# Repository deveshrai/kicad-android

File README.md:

<div align="center">

# KiCad Android

**The real KiCad 10.99 EDA suite for Android and Googlebook OS, running natively on tablets,
foldables and laptops.**

Schematics, PCB layout with the interactive router, 3D viewer and Gerber output, built from
upstream KiCad sources.

-314CB0)

<sub>An ESP32-S3 board in Arduino Uno format, designed on a Galaxy Tab S12+ from an empty schematic to Gerbers, every step driven by Claude Code through KiCad's built-in MCP server.  The screens are real screenshots, from the Android emulator in a laptop-shaped window and from the tablet, shown in drawn device frames.</sub>

</div>

> **Not an official KiCad release.**  This project is not affiliated with or endorsed by the KiCad
> project.  "KiCad" is a trademark of the KiCad project and is used here only to say what this
> software is built from.  Please report problems here, not on KiCad's issue tracker.

## Highlights

- **Full desktop KiCad, not a viewer.**  It includes the project manager, schematic editor, PCB
  editor and push-and-shove router, footprint and symbol editors, Gerber viewer, calculator and
  `kicad-cli`.
- **GPU canvas.**  It runs on KiCad's Vulkan backend, with pointer motion coalesced so the
  interactive router keeps up.
- **Two built-in autorouters.**  **Route > Autoroute** runs
  [KiCadRoutingTools](https://github.com/drandyhaas/KiCadRoutingTools) (Andy Haas's router, with
  its own Python, numpy and scipy) or [Freerouting](https://github.com/freerouting/freerouting) on
  the device.  [More below](#autoroute).
- **Built-in MCP server.**  Turn it on in **Preferences > MCP Server** and Claude Code (on the
  tablet in Termux, or on a computer on the same Wi-Fi) can read and edit your design, route it
  and run DRC while you watch.  It has designed [a whole board](#a-whole-board-over-mcp-esp32-s3-in-uno-format)
  this way, from an empty schematic to Gerbers.
- **3D viewer** with STEP component models, through [gl4es](https://github.com/ptitSeb/gl4es).
- **Desktop-identical output.**  Gerbers and drill files match the macOS build of the same sources
  byte for byte.  [How we checked](docs/CHANGES.md#how-it-was-checked).
- **Keyboard and mouse first**, with KiCad's normal hotkeys, plus touch gestures on the canvas.
- **Libraries included.**  The KiCad 10.0.8 symbol and footprint libraries are bundled.
- **Parts from SnapEDA and other parts sites in one step.**  **File > Import Library Package** adds a downloaded part's symbol, footprint and 3D model to your libraries.  **Export Library Package** packs a library back up to share.  [More below](#parts-from-snapeda-ultra-librarian-and-other-sites).

## From schematic to 3D on a tablet

A complete small board, a CR2032-powered 555 LED blinker, made in the app on a Samsung Galaxy Tab.
The project is in [`work/blinker`](work/blinker).

**1. Schematic.**  Place symbols from the bundled libraries, set values, wire, add power, and run
ERC until it shows 0 errors and 0 warnings.

**2. PCB.**  Pull the footprints in from the schematic and drag them onto the board.  Route them
(the recording imports a Specctra session from Freerouting; since 10.99ae, **Route > Autoroute**
does the same on the device in under a second) and fill the ground zones.

**Or let the built-in autorouter do it.**  Route > Autoroute routes the blinker in under a
second on the tablet, then the zones are refilled.

 Autoroute Board routing the blinker on the tablet: the routes appear, Keep, and the ground zones fill" width="860">

**3. 3D.**  Check the board with its STEP component models.

Full-resolution videos: [schematic](docs/media/video/schematic.mp4),
[PCB](docs/media/video/pcb-layout.mp4), [3D](docs/media/video/3d-blinker.mp4).

## Autoroute

**Route > Autoroute** is one tool for every automatic routing job, as a dialog or docked at the
left of the board editor.  **[The Autoroute manual](docs/AUTOROUTE.md)** covers every option,
with screenshots and recipes.

It has a choice of router:

- **KiCadRoutingTools** (the default): a grid router with rip-up and reroute, fan-out of
  fine-pitch parts, bus routing and plane connections.  It runs on the tablet in a process of its
  own, with python.org's Python 3.14 for Android and numpy, scipy and shapely built for it.
- **Freerouting:** a gridless push-and-shove router with an optimizer.

The tabs:

- **Route:** every unrouted net, or the nets you pick (from a filterable list, or the board
  selection).  Route the picked nets side by side as a bus, or only between two or more parts.
  Choose the layers, and whether to pour the planes and fan out the parts first.
- **Fan Out:** pull short escape tracks out of every pin of dense parts.  "Choose Fine-Pitch
  Parts" ticks every part at 0.5 mm pitch or below.
- **Planes:** copper zones over the whole board, such as GND on In1.Cu and 3V3 on In2.Cu.
- **Optimize:** improve nets that are already routed, your hand-routed ones included.
- **Settings:** how far below the net class sizes the router may go (exactly, down to the
  board's minimums, or down to the fab's), the routing grid, via cost, optimizer passes.

While a run is active the board is locked, so nothing can be edited underneath the router.  The
run shows its steps, the net being routed, progress and the router's output, and can be paused,
resumed or stopped.  At the end it lists the nets still unrouted (tap one to see it) and the whole
run is one undo step: keep it, discard it, or start another run on top.

**Dock to Side** puts the tool in the panel column at the left, the full height of the window
(it takes the Properties panel's place while it's shown); **Undock** turns it back into a dialog.

On the RP2350A board below (2 layers, a 0.4 mm-pitch QFN-60), with the same rules and KiCad's DRC
as the judge:

| | Connections left | DRC errors added | Vias |
|---|---|---|---|
| Freerouting | 86 of 162 | 11 | 63 |
| KiCadRoutingTools, fan-out first | 31 of 162 | 0 | 195 |
| KiCadRoutingTools, 4 layers with GND and 3V3 planes | 20 of 168 | 0 | 199 |

The first run after installing unpacks the router (about 150 MB) and takes a minute.

## Drive it from Claude Code

**Preferences > MCP Server** has a single switch.  Turn it on, copy the ready-made command, and
paste it into a terminal:

```
claude --mcp-config '{"mcpServers":{"kicad":{"type":"http","url":"http://127.0.0.1:27880/mcp","headers":{"Authorization":"Bearer <token>"}}}}'
```

Choose **This device** to connect from the tablet itself (for example Claude Code in Termux), or
**Another computer** to use the tablet's Wi-Fi address.  The status line shows when a client is
connected and what it last did.

 MCP Server: the on switch, This device or Another computer, the address and the claude --mcp-config command with Copy buttons, and the status line" width="860">

What a client can do:
- **See the design:** `kicad_status`, `kicad_open_project`, `kicad_open_editor`, `pcb_board_summary` (every footprint, its position, and the
  unrouted count), and `kicad_screenshot`, a picture of what the app shows, canvas and dialogs included.
- **Change it:** `pcb_move_footprint`, `pcb_run_drc`, and `pcb_autoroute` with
  `pcb_autoroute_status` and `pcb_autoroute_control` (pause, resume, stop, keep, discard): the
  Autoroute tool's options as arguments, the run shown on the tablet.  The changes appear on the
  board as they happen, and each one is an undo step.
- **Do anything else KiCad's IPC API can:** `kicad_api` runs any API command (the API
  kicad-python uses), with `kicad_api_commands` and `kicad_api_describe` to find your way around.
  That covers creating tracks and zones, placing footprints and symbols from the libraries, net
  classes, design rules, and Gerber, drill and PDF exports.  The open project and document are
  filled in when a request leaves them out, so schematic commands such as `GetSchematicNetlist`
  need no arguments.
- **Edit the files directly** if you'd rather: an open schematic or board reloads by itself when
  its file changes on disk, and asks first if there are unsaved edits.

### A whole board over MCP: ESP32-S3 in Uno format

Claude Code designed [this board](work/esp32s3-uno) on the tablet through the MCP server alone.
No tap or keystroke was made on the tablet; adb was used only to record the screen.

- **Schematic:**
  - an ESP32-S3-WROOM-1 with every IO on Uno-style shield headers plus a 2x8 header
  - USB-B like an Uno, and a 7-12 V jack with 5 V and 3.3 V regulators
  - RESET and BOOT buttons, and ON and L LEDs
- **Net classes for each kind of line:**

  | Class | Track | Clearance |
  |---|---|---|
  | Input power (VBUS, VIN) | 0.8 mm | 0.3 mm |
  | 5 V and 3.3 V rails | 0.6 mm | 0.25 mm |
  | GND (plus pours on both layers) | 0.5 mm | 0.2 mm |
  | USB differential pair | 0.3 mm | 0.2 mm |
  | Analog | 0.25 mm | 0.3 mm |
  | Digital, I2C, UART, GPIO | 0.25 mm | 0.2 mm |

- **Board:**
  - Placement, design rules, the built-in autorouter (107 of 107 connections) and GND pours.
  - DRC with no errors.
  - Gerbers, drill files and 3D renders, all exported over MCP.

The scripts, the finished project with its fab files, and the full log of the 465 MCP calls are
in [`work/esp32s3-uno`](work/esp32s3-uno).

<table>
<tr>
<td width="50%"></td>
<td width="50%"></td>
</tr>
<tr>
<td>Autorouting over MCP, then the GND pours (10x speed; <a href="https://github.com/deveshrai/kicad-android/releases/download/android-10.99ag/esp32s3-uno-route.mp4">MP4</a>)</td>
<td>The finished board in the board editor</td>
</tr>
<tr>
<td></td>
<td></td>
</tr>
<tr>
<td>3D render, top (exported over MCP)</td>
<td>3D render, bottom</td>
</tr>
</table>

## See it run

<table>
<tr>
<td width="50%" align="center">
<br>
<sub><b>Touch:</b> pinch to zoom, two fingers to pan, three-finger tap to fit</sub>
</td>
<td width="50%" align="center">
<br>
<sub><b>3D viewer:</b> drag to orbit the board and its STEP models</sub>
</td>
</tr>
<tr>
<td width="50%" align="center">
<br>
<sub><b>3D viewer</b> on a Galaxy Z Fold, with an RP2350 board</sub>
</td>
<td width="50%" align="center">
<br>
<sub>The blinker's STEP models up close</sub>
</td>
</tr>
<tr>
<td width="50%" align="center">
<br>
<sub><b>PCB editor</b> on the Fold's inner screen</sub>
</td>
<td width="50%" align="center">
<br>
<sub><b>Schematic editor</b> with a KiCad demo project</sub>
</td>
</tr>
</table>

## Install

1. Download the APK from [**Releases**](https://github.com/deveshrai/kicad-android/releases).
   It is for Android and Googlebook OS: it needs an arm64 device with Android 10 or newer, or
   an arm64 Googlebook.  It is tested on Galaxy tablets and foldables; it has not been tried on
   a Googlebook yet, so please report how it goes.
2. Let your browser or file manager install apps, then open the APK.
3. On first start, grant **All files access**, so KiCad can open projects in shared storage
   (`Documents`).

A keyboard and mouse are recommended: a Googlebook's own, a Bluetooth or USB keyboard, or
Samsung DeX.

<details>
<summary><b>Libraries and 3D models</b></summary>

The symbol and footprint libraries and the project templates come with the app.  The 3D models
don't (663 MB to download, 3.2 GB installed): the setup wizard's **Library Files** page, shown once
at first start and any time from **Preferences > Run Setup Wizard**, offers to:
- download the 3D models from [KiCad's library repositories](https://gitlab.com/kicad/libraries);
- update the symbol and footprint libraries and templates to the newest release there;
- install libraries from zip or tar.gz archives: KiCad's repository archives, or the symbols,
  footprints, 3dmodels and template folders of a desktop KiCad.

Parts imported with **Import Library Package** bring their own 3D models.

</details>

## Parts from SnapEDA, Ultra Librarian and other sites

Download the part's **KiCad** zip in the browser, then in the project manager choose
**File > Import Library Package...** and pick the zip from Downloads.  Choose **All Projects**
or **This Project** (the files are then copied into the project folder, so they travel with it).
The symbol, footprint and 3D model are ready to place straight away:

- The footprint's 3D model path, which usually points into the author's own computer, is
  pointed at the unpacked model.
- The symbol's footprint field is pointed at the footprint library.
- The libraries are added to the library tables and loaded in the open editors.
- Importing the same zip again updates the part.

**File > Export Library Package...** does the reverse.  It saves a symbol library, the footprints
its symbols use and their 3D models as one zip, ready to import on another device or into
desktop KiCad.

<table>
<tr>
<td width="50%"> Import Library Package on the tablet: the Android file picker finds the SnapEDA zip, All Projects, and the summary of what was added"></td>
<td width="50%"></td>
</tr>
<tr>
<td>Importing SnapEDA's ESP32-S31-WROOM-1 zip on the tablet</td>
<td>The imported footprint with its 3D model, trial-placed on a board</td>
</tr>
</table>

Both are also MCP tools (`kicad_import_library_package`, `kicad_export_library_package`), so
Claude Code can bring in the parts a design needs.

## Using it

| Input | What it does |
|---|---|
| Mouse and keyboard | Same as KiCad on the desktop, hotkeys included |
| One finger on the canvas | Left mouse button: click, select, drag, draw tracks and wires |
| Two fingers | Pinch to zoom around your fingers; drag to pan |
| Three-finger tap | Zoom to fit |

## How it works

KiCad's UI is written against wxWidgets, which has no Android port.  This build runs wxWidgets'
**Qt port** on **Qt 6 for Android**.  KiCad draws its canvas with **Vulkan** and its 3D view with
**OpenGL 2.1 via gl4es**.  It stays close to upstream: everything is a patch series against exact
upstream revisions.

| Layer | Changes |
|---|---|
| KiCad | [`patches/kicad`](patches/kicad): Android platform layer, Vulkan canvas, touch, 3D viewer, a few general fixes |
| wxWidgets (wxQt) | [`patches/wxwidgets`](patches/wxwidgets): input, dialogs, fonts, Android pickers and intents, crash fixes |
| Qt for Android | [`patches/qtbase`](patches/qtbase): faster window composition, input-method fixes |
| MCP server | part of [`patches/kicad`](patches/kicad) (patch 0031): an MCP server on KiCad's IPC API, with a one-page settings panel |
| Freerouting | [`patches/freerouting`](patches/freerouting): its routing core built for Android's Java runtime, driven by [`android/autorouter`](android/autorouter) |
| KiCadRoutingTools | unchanged, run by [`android/router`](android/router) in a process of its own; [`scripts/build-python-android.sh`](scripts/build-python-android.sh) builds it, Python 3.14, numpy, scipy (no Fortran; OpenBLAS with C LAPACK) and shapely (GEOS) for Android, with one scipy patch in [`patches/python`](patches/python) |

**[Read the full write-up of the changes →](docs/CHANGES.md)**

## Status

This is a development build of KiCad master.  It works for real design work with a keyboard and
mouse.  Known rough edges:

- Some dialogs open partly under the status bar, or with their buttons clipped, at tablet scales.
- Docked panels can cover the canvas on smaller screens.  Close them from **View > Panels**.
- The soft keyboard can cover the field being edited.
- The 3D viewer doesn't take touch gestures yet; it gets the standard mouse emulation.

The working notes and the full list are in [`docs/HANDOVER.md`](docs/HANDOVER.md).

## Building from source

The build runs on macOS (Apple silicon).  It needs:

- Android NDK r29, SDK build tools 35/36 and a JDK 17
- Qt 6.12.0 for Android arm64 and for macOS
- vcpkg

Then run:

```sh
scripts/build-deps.sh          # vcpkg dependencies for arm64-android
scripts/build-wxqt-android.sh  # wxWidgets (wxQt) + patches/wxwidgets
scripts/build-qtforandroid.sh  # Qt's Android platform plugin + patches/qtbase
scripts/build-gl4es.sh         # libGL.so for the 3D viewer
scripts/build-kicad-android.sh # KiCad + patches/kicad
scripts/build-kicad-apk.sh     # the APK
```

- [`SOURCES.md`](SOURCES.md) lists the exact upstream revision each patch series applies to.
- [`PLAN.md`](PLAN.md) covers the architecture.
- [`docs/HANDOVER.md`](docs/HANDOVER.md) covers the toolchain, devices and test setup.

Most of this port was written with an AI coding assistant (Claude); see the commit trailers.

## Licence

- This repository's own files are licensed **GPL-3.0-or-later** ([`LICENSE`](LICENSE)).
- Each patch carries the licence of the project it modifies:
  - KiCad: GPL-3.0-or-later
  - wxWidgets: wxWindows Library Licence
  - Qt: LGPL-3.0
- The APK combines KiCad with Qt (LGPL-3.0), wxWidgets, gl4es (MIT) and the libraries in
  [`SOURCES.md`](SOURCES.md), each under its own licence.  The router process adds
  KiCadRoutingTools (MIT), CPython (PSF), numpy, scipy and shapely (BSD), OpenBLAS (BSD) and GEOS
  (LGPL-2.1, as a shared library).  The bundled KiCad libraries are
  CC-BY-SA-4.0 with the KiCad library exception.
- The corresponding source for every published APK is this repository at the release tag, together
  with the upstream revisions in `SOURCES.md`.

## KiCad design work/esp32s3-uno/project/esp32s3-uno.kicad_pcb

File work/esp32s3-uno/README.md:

# ESP32-S3 Uno: a board designed through KiCad's MCP server

An Arduino Uno-format board for the ESP32-S3-WROOM-1. Claude Code built it on the tablet,
start to finish, through KiCad Android's built-in MCP server. Every design change went through
MCP (`kicad_api` and the `pcb_*` tools); adb was used only for screen recording and screenshots.

- **Shield headers** J1-J4, mounting holes and outline sit where an Uno has them (from KiCad's Arduino Uno template).
- **Pin map:**
  - A0-A3 are IO1-IO4.
  - SDA/SCL are IO8/IO9, on both J3 and J2.
  - D2-D13 are IO17, IO16, IO15, IO7, IO6, IO5, IO21, IO14, IO10, IO11, IO13 and IO12.
  - TX/RX go to the module's UART0.
- **J5** (2x8) carries the rest: IO0, IO18, IO35-IO42 and IO45-IO48, plus 3V3 and GND.
- **Power:**
  - USB-B like an Uno, through a 500 mA polyfuse and a Schottky diode to 5 V. USB D+/D- go to the S3's native USB.
  - The 7-12 V barrel jack goes through a reverse-protection diode and an AMS1117-5.0 regulator.
  - An AMS1117-3.3 makes 3V3.
- **Controls and LEDs:** RESET (EN) and BOOT (IO0) buttons with pull-ups, the EN RC delay, an ON LED, and an L LED on D13.
- **Antenna:** the module's antenna overhangs the right-hand edge, so its keepout lies off the board. A custom rule tells DRC to ignore the courtyard keepout.

## Net classes

Track widths assume 1 oz copper on a 2-layer 1.6 mm board (IPC-2221 outer layers, 10 °C rise).

| Class | Nets | Track | Clearance | Via |
|---|---|---|---|---|
| Power_In | VBUS, VBUS_F, VIN_RAW, VIN (USB 5 V and the 7-12 V jack, up to 1 A) | 0.80 mm | 0.30 mm | 0.8/0.4 mm |
| Power | +5V, +3V3 (the ESP32-S3 peaks at about 0.5 A) | 0.60 mm | 0.25 mm | 0.8/0.4 mm |
| GND | GND (mostly carried by the pours on both layers) | 0.50 mm | 0.20 mm | 0.8/0.4 mm |
| USB | USB_D+, USB_D- (full-speed pair, 0.2 mm gap) | 0.30 mm | 0.20 mm | 0.6/0.3 mm |
| Analog | A0-A3 (extra clearance against coupling) | 0.25 mm | 0.30 mm | 0.6/0.3 mm |
| Digital | D2-D13 | 0.25 mm | 0.20 mm | 0.6/0.3 mm |
| I2C | SDA, SCL | 0.25 mm | 0.20 mm | 0.6/0.3 mm |
| UART | TX, RX | 0.25 mm | 0.20 mm | 0.6/0.3 mm |
| GPIO | IO18, IO35-IO48 | 0.25 mm | 0.20 mm | 0.6/0.3 mm |
| Control | EN, IO0, LED nets | 0.25 mm | 0.20 mm | 0.6/0.3 mm |

**Board minimums:** 0.15 mm track and 0.2 mm drill. The router necks tracks down to 0.19 mm where they leave the module's 1.27 mm-pitch pads, and the module footprint has 0.2 mm thermal vias.

**Result:**
- 107 of 107 connections routed (57 vias), with GND pours on both layers.
- DRC finds no errors.
- The warnings are all expected:
  - silkscreen clipped by the deliberately overhanging jack, USB-B and antenna, and by the template's J4;
  - footprints that differ from the library copies (the template's sockets, and U1's moved reference).

## How it was built (in order)

Each step is a script that talks to the tablet's MCP server through `mcp_client.py`. Over USB, forward the port first with `adb forward tcp:27880 tcp:27880`.

1. `build_schematic.py`: places every symbol and joins each pin to its net by a label or a power symbol (`PlaceSymbolFromLibrary`, `CreateItems`, `UpdateItems`). The netlist is then exported (`RunSchematicJobExportNetlist`) and imported into the template board (`ImportNetlist`).
2. `set_netclasses.py`: net classes and their pattern assignments (`SetNetClasses`, `SetNetClassAssignments`).
3. `design_rules.py`: minimum sizes, plus the track and via size lists (`SetBoardDesignRules`).
4. `place_pcb.py`: placement (`pcb_move_footprint`), moved reference texts, and the module courtyard rule (`SetCustomDesignRules`).
5. `route.py`: the integrated autorouter (`pcb_autoroute`). It removes copper pours first, because the router routes much worse around a filled GND pour (23 connections unrouted instead of 0).
6. `zones.py`: GND pours on F.Cu and B.Cu (`CreateItems` Zone, `RefillZones`). Then `pcb_run_drc`.
7. `models_3d.py`: points `KICAD10_3DMODEL_DIR` at `${KIPRJMOD}/3dmodels` with a project text variable (`SetTextVariables`). KiCad Android does not bundle the 3D library.
8. `export.py`: Gerbers, drill and 3D renders (`RunBoardJobExport*`). The outputs are in `project/fab` and `project/render-*.png`.

`mcp-log.jsonl.gz` records every MCP request and reply of the session (465 tool calls).

### 3D models

`project/3dmodels` is not in the repository. To render the board with parts:
- Download these files from [kicad-packages3D](https://gitlab.com/kicad/libraries/kicad-packages3D) (tag 10.0.8) into `project/3dmodels/<Library>.3dshapes/`:
  - SW_SPST_PTS645Sx43SMTR92, C_0805_2012Metric, BarrelJack_Horizontal
  - PinHeader_2x08_P2.54mm_Vertical, D_SMA, Fuse_1206_3216Metric, LED_0805_2012Metric
  - SOT-223, R_0805_2012Metric, ESP32-S3-WROOM-1
  - PinSocket_1x06/1x08/1x10_P2.54mm_Vertical
- The library has no model for the OST USB-B connector.
- The template's sockets still point at KiCad 9 `.wrl` files, so they render without bodies.

## Known blemishes

- In the schematic, C5 sits on the title block border.

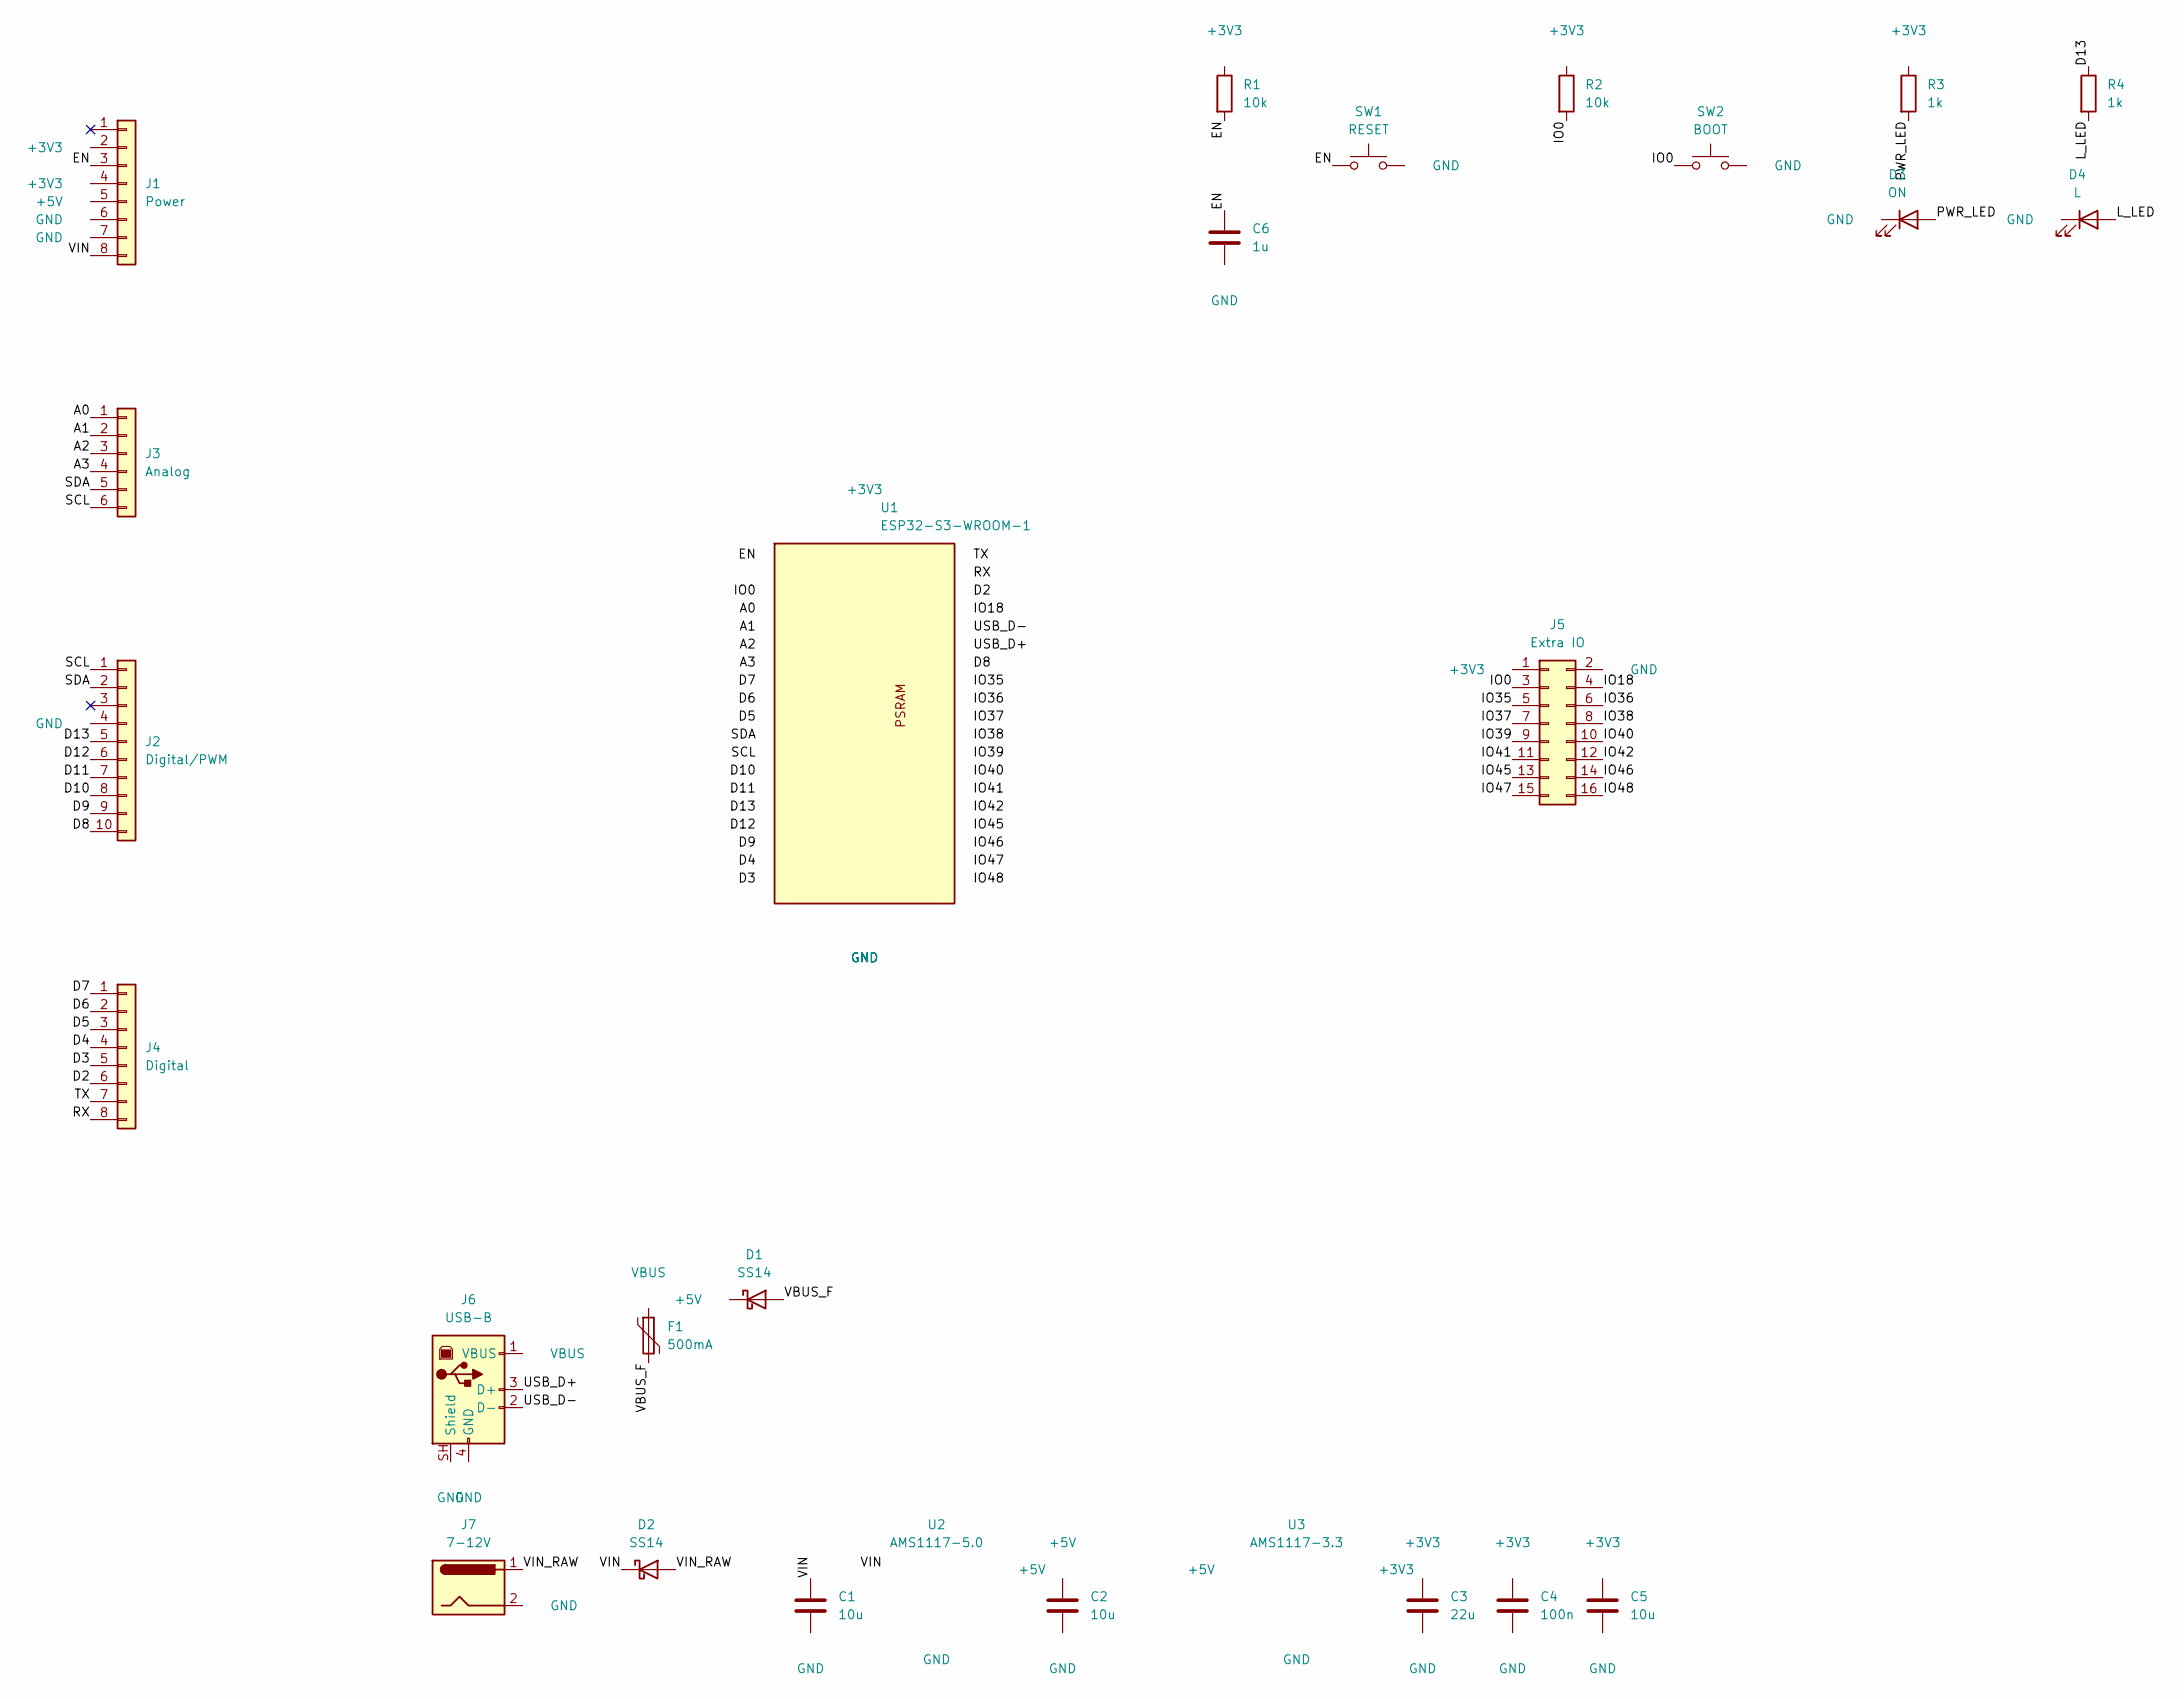
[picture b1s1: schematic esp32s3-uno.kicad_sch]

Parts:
C1, C2, C5: 10u; C_0805_2012Metric
C3: 22u; C_0805_2012Metric
C4: 100n; C_0805_2012Metric
C6: 1u; C_0805_2012Metric
D1, D2: SS14; D_SMA
D3: ON; LED_0805_2012Metric
D4: L; LED_0805_2012Metric
F1: 500mA; Fuse_1206_3216Metric
J1: Power; PinSocket_1x08_P2.54mm_Vertical
J2: Digital/PWM; PinSocket_1x10_P2.54mm_Vertical
J3: Analog; PinSocket_1x06_P2.54mm_Vertical
J4: Digital; PinSocket_1x08_P2.54mm_Vertical
J5: Extra IO; PinHeader_2x08_P2.54mm_Vertical
J6: USB-B; USB_B_OST_USB-B1HSxx_Horizontal
J7: 7-12V; BarrelJack_Horizontal
R1, R2: 10k; R_0805_2012Metric
R3, R4: 1k; R_0805_2012Metric
SW1: RESET; SW_SPST_PTS645Sx43SMTR92
SW2: BOOT; SW_SPST_PTS645Sx43SMTR92
U1: ESP32-S3-WROOM-1
U2: AMS1117-5.0; SOT-223-3_TabPin2
U3: AMS1117-3.3; SOT-223-3_TabPin2

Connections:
+3V3: C3.1, C4.1, C5.1, J1.2, J1.4, J5.1, R1.1, R2.1, R3.1, U1.2 (3V3), U3.2 (VO)
+5V: C2.1, D1.1 (K), J1.5, U2.2 (VO), U3.3 (VI)
/A0: J3.1, U1.39 (IO1)
/A1: J3.2, U1.38 (IO2)
/A2: J3.3, U1.15 (IO3)
/A3: J3.4, U1.4 (IO4)
/D2: J4.6, U1.10 (IO17)
/D3: J4.5, U1.9 (IO16)
/D4: J4.4, U1.8 (IO15)
/D5: J4.3, U1.7 (IO7)
/D6: J4.2, U1.6 (IO6)
/D7: J4.1, U1.5 (IO5)
/D8: J2.10, U1.23 (IO21)
/D9: J2.9, U1.22 (IO14)
/D10: J2.8, U1.18 (IO10)
/D11: J2.7, U1.19 (IO11)
/D12: J2.6, U1.21 (IO13)
/D13: J2.5, R4.1, U1.20 (IO12)
/EN: C6.1, J1.3, R1.2, SW1.1, U1.3 (EN)
/IO0: J5.3, R2.2, SW2.1, U1.27 (IO0)
/IO18: J5.4, U1.11 (IO18)
/IO35: J5.5, U1.28 (IO35)
/IO36: J5.6, U1.29 (IO36)
/IO37: J5.7, U1.30 (IO37)
/IO38: J5.8, U1.31 (IO38)
/IO39: J5.9, U1.32 (IO39)
/IO40: J5.10, U1.33 (IO40)
/IO41: J5.11, U1.34 (IO41)
/IO42: J5.12, U1.35 (IO42)
/IO45: J5.13, U1.26 (IO45)
/IO46: J5.14, U1.16 (IO46)
/IO47: J5.15, U1.24 (IO47)
/IO48: J5.16, U1.25 (IO48)
/L_LED: D4.2 (A), R4.2
/PWR_LED: D3.2 (A), R3.2
/RX: J4.8, U1.36 (RXD0)
/SCL: J2.1, J3.6, U1.17 (IO9)
/SDA: J2.2, J3.5, U1.12 (IO8)
/TX: J4.7, U1.37 (TXD0)
/USB_D+: J6.3 (D+), U1.14 (USB_D+)
/USB_D-: J6.2 (D-), U1.13 (USB_D-)
/VBUS_F: D1.2 (A), F1.2
/VIN: C1.1, D2.1 (K), J1.8, U2.3 (VI)
/VIN_RAW: D2.2 (A), J7.1
GND: C1.2, C2.2, C3.2, C4.2, C5.2, C6.2, D3.1 (K), D4.1 (K), J1.6, J1.7, J2.4, J5.2, J6.4 (GND), J6.SH (Shield), J7.2, SW1.2, SW2.2, U1.1 (GND), U1.40 (GND), U1.41 (GND), U2.1 (GND), U3.1 (GND)
VBUS: F1.1, J6.1 (VBUS)

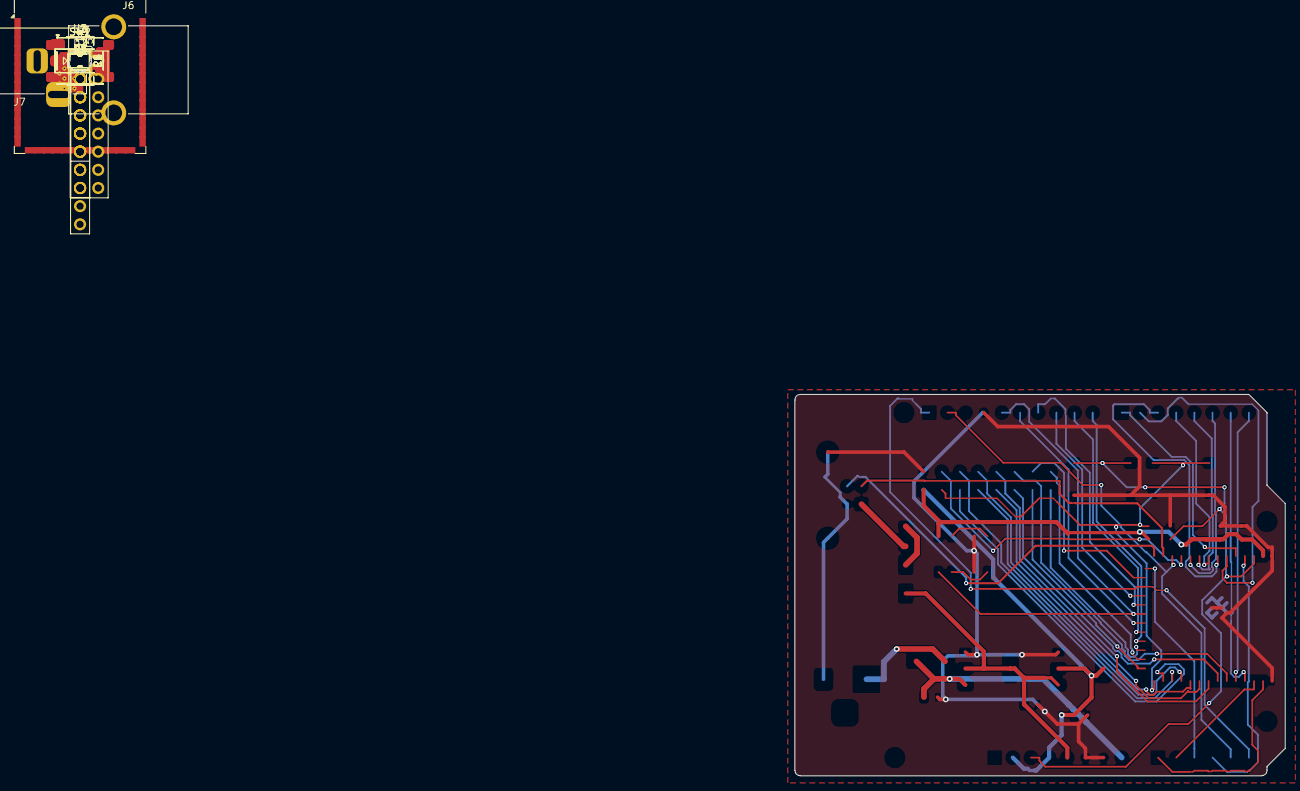
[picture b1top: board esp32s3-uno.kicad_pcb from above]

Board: 2 copper layers, 68.6 x 53.3 mm, 31 parts (0 on the bottom side), 46 nets.

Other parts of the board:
MH1, MH2, MH3, MH4: MountingHole_3.2mm

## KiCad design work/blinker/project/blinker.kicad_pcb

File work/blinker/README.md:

# 555 LED blinker (end-to-end test project)

A CR2032-powered 5 mm LED blinker: an ICM7555 (CMOS 555, runs from 2 V) in astable mode,
R1 1k, R2 47k, C1 10 µF (≈1.5 Hz), C2 10 nF on CV, C3 100 nF decoupling, R3 220 Ω and a red LED,
an on/off slide switch, all through-hole.

Made on a Galaxy Tab (2026-11-06) to test the whole flow in the Android app:
New Project (Android save picker) → schematic (generated by `gen_sch.py`, ERC 0) →
Update PCB from Schematic → placement (`place_pcb.py`) → Freerouting (Specctra export/import) →
zone fill, DRC (0 violations, schematic parity OK) → 3D viewer with STEP models.

`project/` holds the finished files.

## README recordings

The schematic, PCB and 3D GIFs in the top-level README were recorded on the tablet from a demo
copy of this project:

- `BLINKER_DEMO=1 gen_sch.py out.kicad_sch` leaves out the LED stage (R3, D1), so it can be drawn
  in the app.
- `demo_pcb.py finished.kicad_pcb out.kicad_pcb` removes the tracks and zone fills and lines the
  footprints up beside the board.

The recording was driven over adb: keys, `input text`, and `tools/touchinject` for drags, pinches,
mouse hover and clicks.  It used `screenrecord`, and was cut with ffmpeg (`mpdecimate` drops idle
frames).

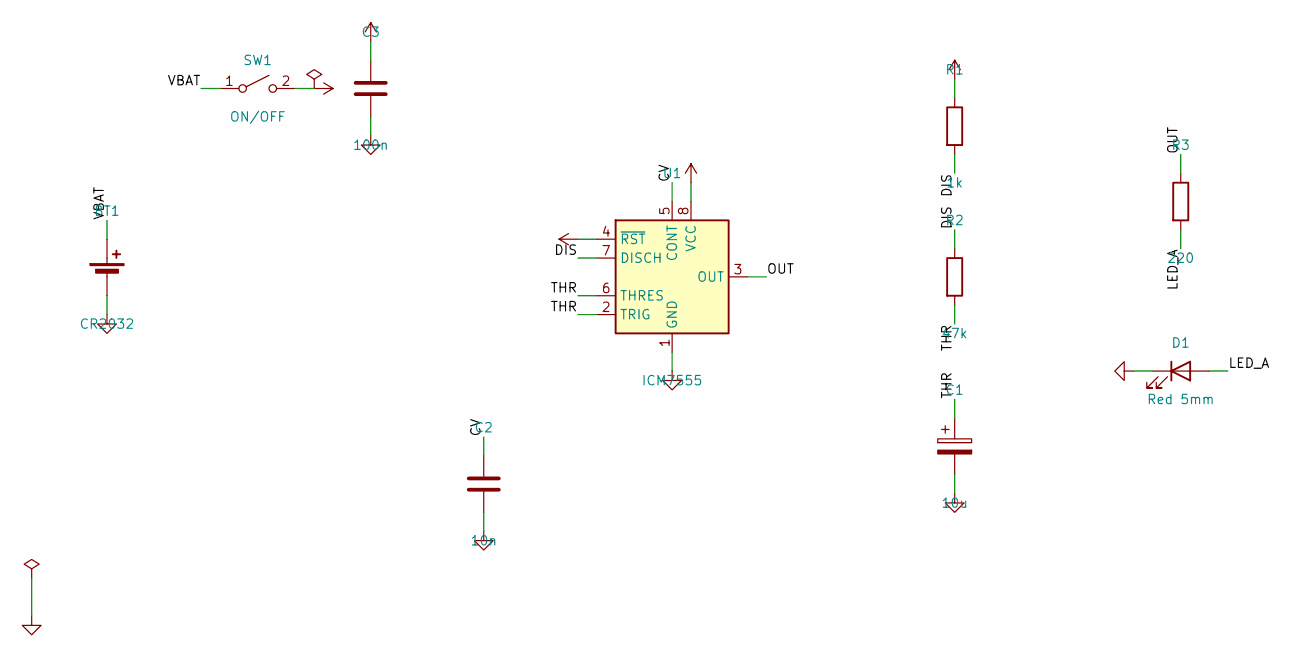
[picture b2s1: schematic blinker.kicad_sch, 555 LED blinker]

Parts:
BT1: CR2032; BatteryHolder_Keystone_103_1x20mm
C1: 10u; CP_Radial_D5.0mm_P2.00mm
C2: 10n; C_Disc_D3.0mm_W1.6mm_P2.50mm
C3: 100n; C_Disc_D3.0mm_W1.6mm_P2.50mm
D1: Red 5mm; LED_D5.0mm
R1: 1k; R_Axial_DIN0207_L6.3mm_D2.5mm_P10.16mm_Horizontal
R2: 47k; R_Axial_DIN0207_L6.3mm_D2.5mm_P10.16mm_Horizontal
R3: 220; R_Axial_DIN0207_L6.3mm_D2.5mm_P10.16mm_Horizontal
SW1: ON/OFF; SW_DIP_SPSTx01_Slide_9.78x4.72mm_W7.62mm_P2.54mm
U1: ICM7555; DIP-8_W7.62mm

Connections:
/CV: C2.1, U1.5 (CONT)
/DIS: R1.2, R2.1, U1.7 (DISCH)
/LED_A: D1.2 (A), R3.2
/OUT: R3.1, U1.3 (OUT)
/THR: C1.1, R2.2, U1.2 (TRIG), U1.6 (THRES)
/VBAT: BT1.1 (+), SW1.1 (A)
GND: BT1.2 (-), C1.2, C2.2, C3.2, D1.1 (K), U1.1 (GND)
VCC: C3.1, R1.1, SW1.2 (B), U1.4 (~RST), U1.8 (VCC)

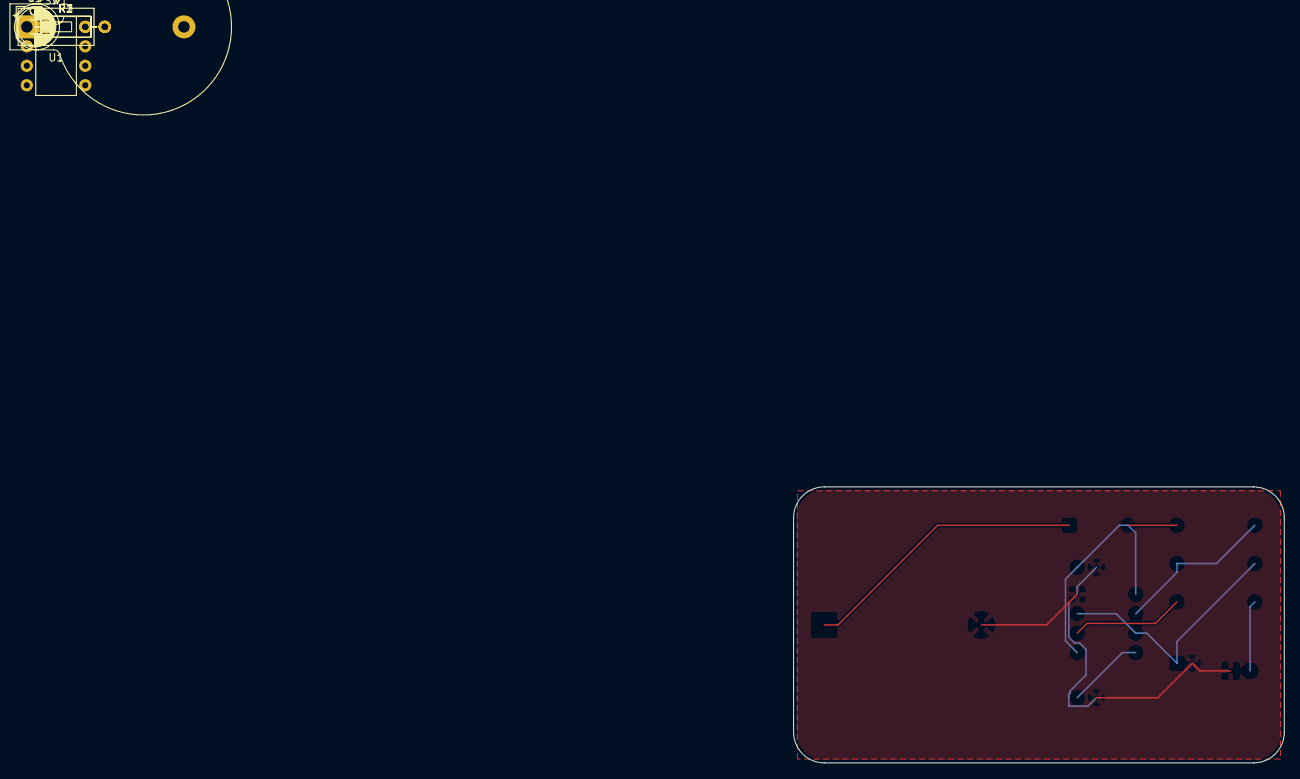
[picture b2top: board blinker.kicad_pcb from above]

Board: 2 copper layers, 64.0 x 36.0 mm, 10 parts (0 on the bottom side), 8 nets.

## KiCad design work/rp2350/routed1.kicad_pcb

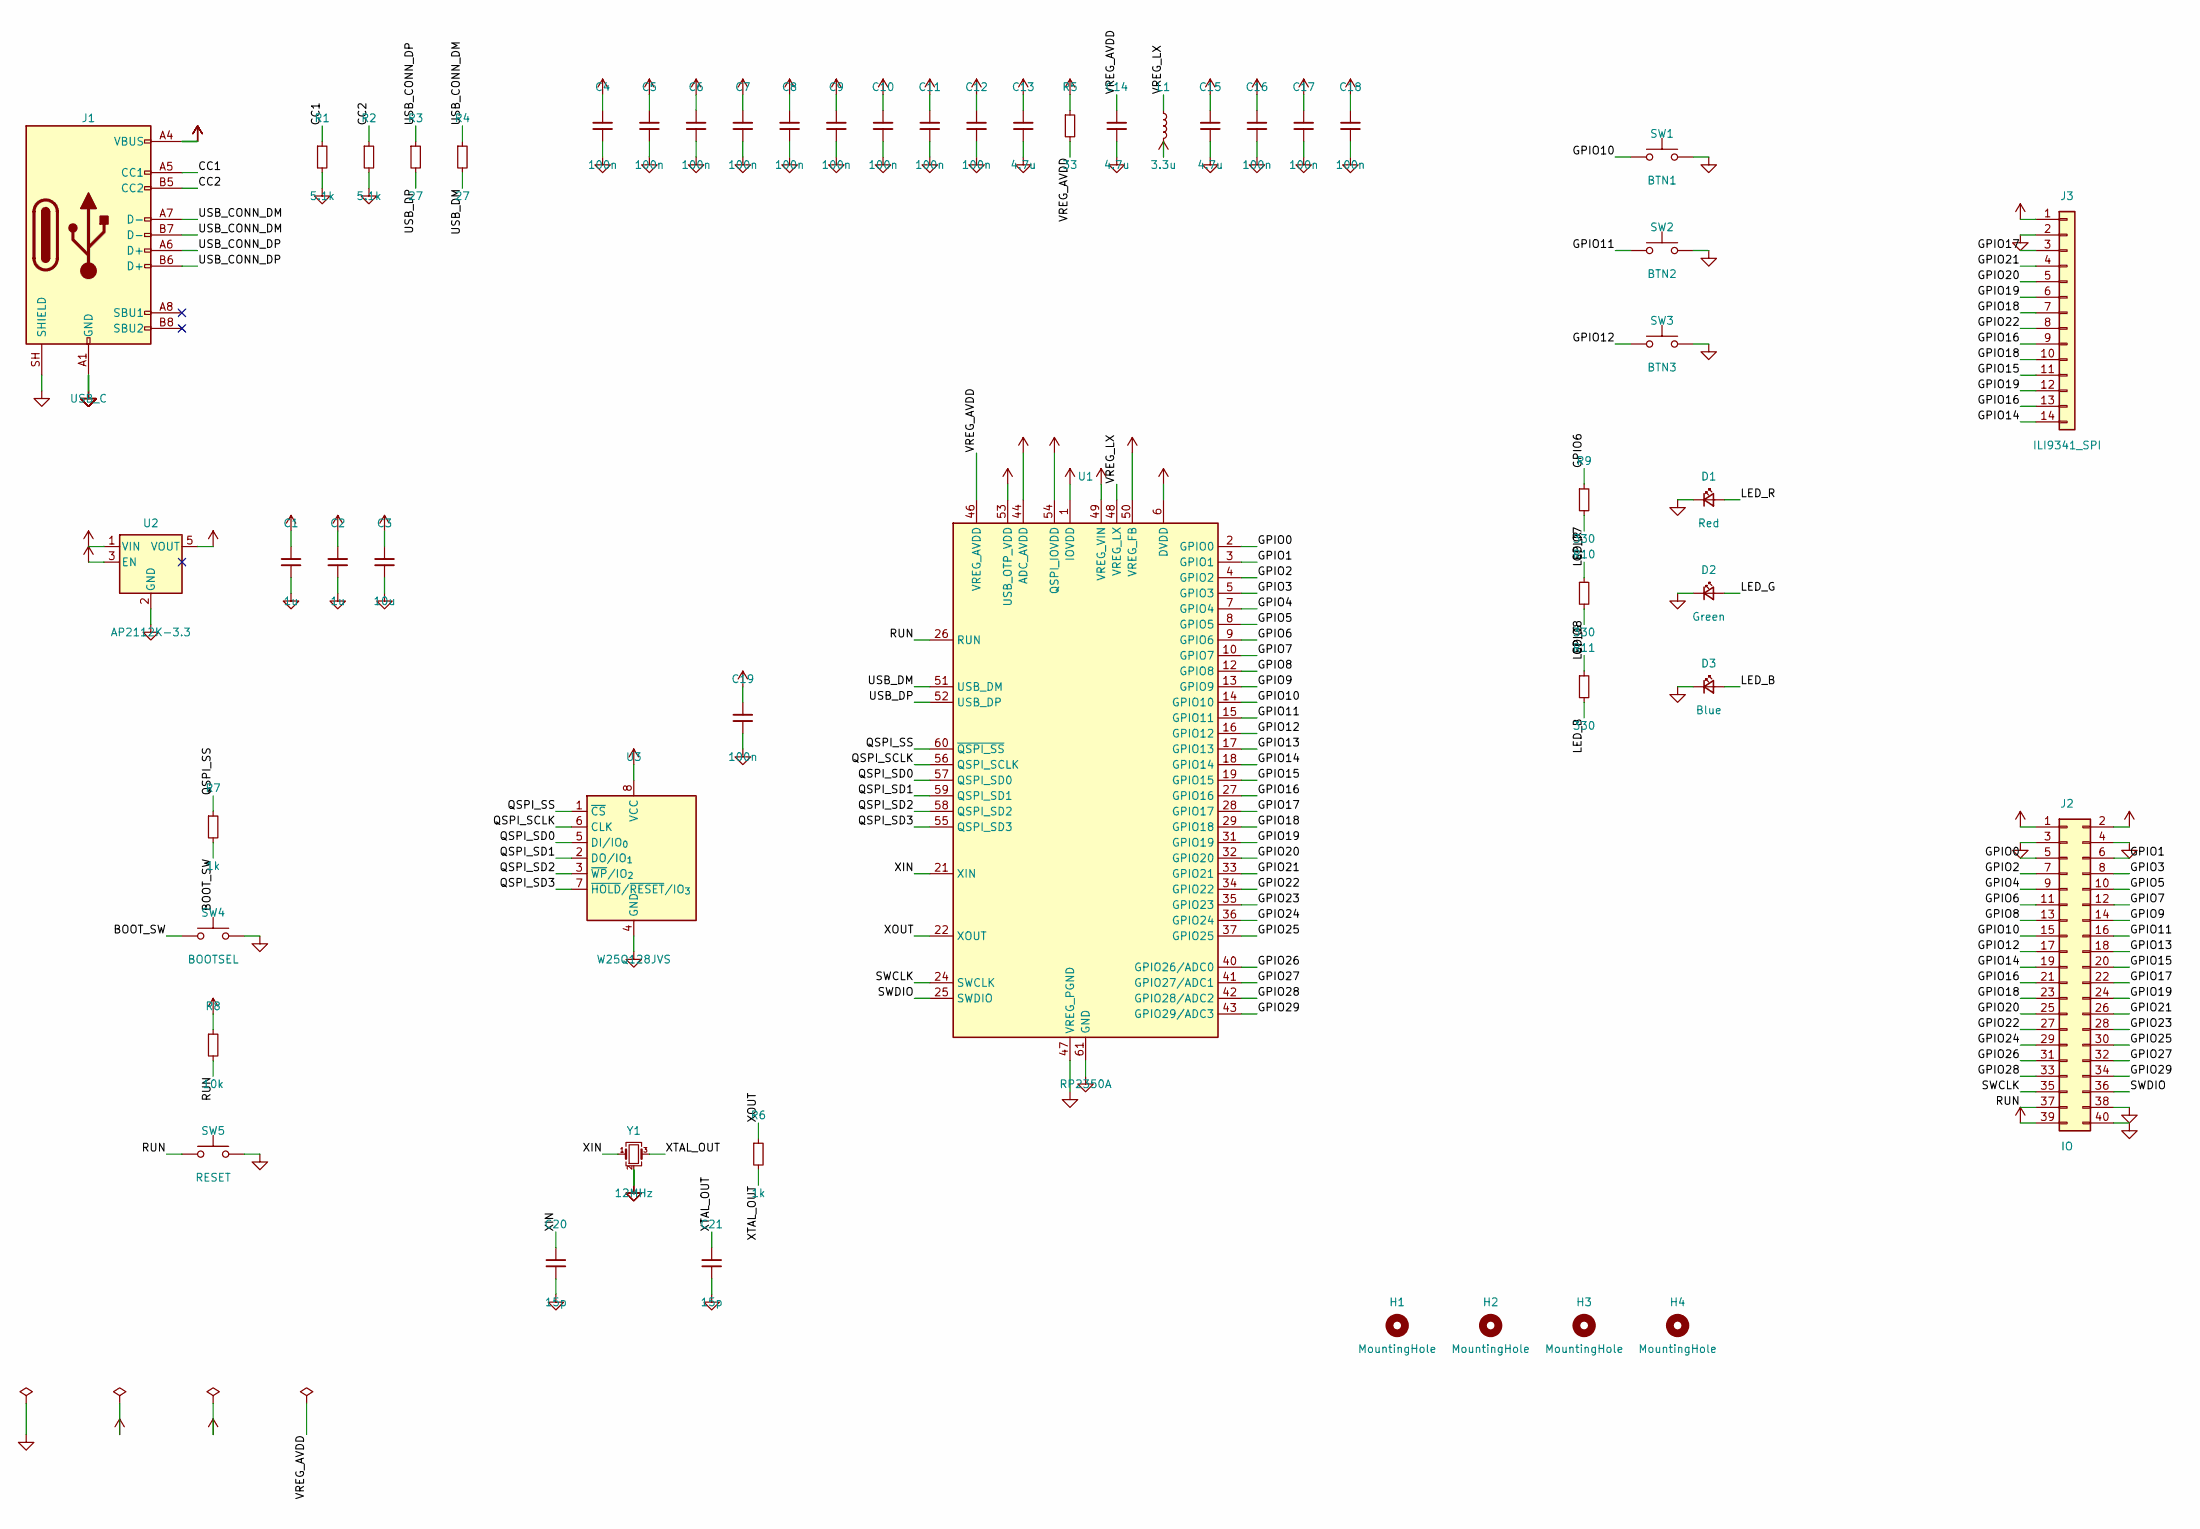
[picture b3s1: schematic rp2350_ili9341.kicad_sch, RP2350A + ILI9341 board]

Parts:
C1, C2: 1u; C_0603_1608Metric; MPN CL10A105KB8NNNC
C3: 10u; C_0805_2012Metric; MPN CL21A106KAYNNNE
C4, C5, C6, C7, C8, C9, C10, C11, C12, C16, C17, C18, C19: 100n; C_0603_1608Metric; MPN CL10B104KB8NNNC
C13, C14, C15: 4.7u; C_0805_2012Metric; MPN CL21A475KAQNNNE
C20, C21: 15p; C_0603_1608Metric; MPN CL10C150JB8NNNC
D1: Red; LED_0603_1608Metric; MPN APT1608EC
D2: Green; LED_0603_1608Metric; MPN APT1608SGC
D3: Blue; LED_0603_1608Metric; MPN APT1608QBC/D
H1, H2, H3, H4: MountingHole; MountingHole_2.7mm_M2.5
J1: USB_C; USB_C_Receptacle_HRO_TYPE-C-31-M-12; MPN TYPE-C-31-M-12
J2: IO; PinHeader_2x20_P2.54mm_Vertical; MPN PRPC020DAAN-RC
J3: ILI9341_SPI; PinSocket_1x14_P2.54mm_Vertical; MPN PPTC141LFBN-RC
L1: 3.3u; L_Abracon_AOTA-B201610S; MPN AOTA-B201610S3R3-101-T
R1, R2: 5.1k; R_0603_1608Metric; MPN RC0603FR-075K1L
R3, R4: 27; R_0603_1608Metric; MPN RC0603FR-0727RL
R5: 33; R_0603_1608Metric; MPN RC0603FR-0733RL
R6, R7: 1k; R_0603_1608Metric; MPN RC0603FR-071KL
R8: 10k; R_0603_1608Metric; MPN RC0603FR-0710KL
R9, R10, R11: 330; R_0603_1608Metric; MPN RC0603FR-07330RL
SW1: BTN1; SW_SPST_TL3342; MPN TL3342F160QG
SW2: BTN2; SW_SPST_TL3342; MPN TL3342F160QG
SW3: BTN3; SW_SPST_TL3342; MPN TL3342F160QG
SW4: BOOTSEL; SW_SPST_TL3342; MPN TL3342F160QG
SW5: RESET; SW_SPST_TL3342; MPN TL3342F160QG
U1: RP2350A; QFN-60-1EP_7x7mm_P0.4mm_EP3.4x3.4mm; MPN RP2350A
U2: AP2112K-3.3; SOT-23-5; MPN AP2112K-3.3TRG1
U3: W25Q128JVS; SOIC-8_5.3x5.3mm_P1.27mm; MPN W25Q128JVSIQ
Y1: 12MHz; Crystal_SMD_3225-4Pin_3.2x2.5mm; MPN ABM8-272-T3

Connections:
+1V1: C15.1, C16.1, C17.1, C18.1, L1.2, U1.6 (DVDD), U1.23 (DVDD), U1.39 (DVDD), U1.50 (VREG_FB)
+3V3: C2.1, C3.1, C4.1, C5.1, C6.1, C7.1, C8.1, C9.1, C10.1, C11.1, C12.1, C13.1, C19.1, J2.2, J2.39, J3.1, R5.1, R8.1, U1.1 (IOVDD), U1.11 (IOVDD), U1.20 (IOVDD), U1.30 (IOVDD), U1.38 (IOVDD), U1.44 (ADC_AVDD), U1.45 (IOVDD), U1.49 (VREG_VIN), U1.53 (USB_OTP_VDD), U1.54 (QSPI_IOVDD), U2.5 (VOUT), U3.8 (VCC)
/BOOT_SW: R7.2, SW4.1
/CC1: J1.A5 (CC1), R1.1
/CC2: J1.B5 (CC2), R2.1
/GPIO0: J2.5, U1.2 (GPIO0)
/GPIO1: J2.6, U1.3 (GPIO1)
/GPIO2: J2.7, U1.4 (GPIO2)
/GPIO3: J2.8, U1.5 (GPIO3)
/GPIO4: J2.9, U1.7 (GPIO4)
/GPIO5: J2.10, U1.8 (GPIO5)
/GPIO6: J2.11, R9.1, U1.9 (GPIO6)
/GPIO7: J2.12, R10.1, U1.10 (GPIO7)
/GPIO8: J2.13, R11.1, U1.12 (GPIO8)
/GPIO9: J2.14, U1.13 (GPIO9)
/GPIO10: J2.15, SW1.1, U1.14 (GPIO10)
/GPIO11: J2.16, SW2.1, U1.15 (GPIO11)
/GPIO12: J2.17, SW3.1, U1.16 (GPIO12)
/GPIO13: J2.18, U1.17 (GPIO13)
/GPIO14: J2.19, J3.14, U1.18 (GPIO14)
/GPIO15: J2.20, J3.11, U1.19 (GPIO15)
/GPIO16: J2.21, J3.9, J3.13, U1.27 (GPIO16)
/GPIO17: J2.22, J3.3, U1.28 (GPIO17)
/GPIO18: J2.23, J3.7, J3.10, U1.29 (GPIO18)
/GPIO19: J2.24, J3.6, J3.12, U1.31 (GPIO19)
/GPIO20: J2.25, J3.5, U1.32 (GPIO20)
/GPIO21: J2.26, J3.4, U1.33 (GPIO21)
/GPIO22: J2.27, J3.8, U1.34 (GPIO22)
/GPIO23: J2.28, U1.35 (GPIO23)
/GPIO24: J2.29, U1.36 (GPIO24)
/GPIO25: J2.30, U1.37 (GPIO25)
/GPIO26: J2.31, U1.40 (GPIO26/ADC0)
/GPIO27: J2.32, U1.41 (GPIO27/ADC1)
/GPIO28: J2.33, U1.42 (GPIO28/ADC2)
/GPIO29: J2.34, U1.43 (GPIO29/ADC3)
/LED_B: D3.2 (A), R11.2
/LED_G: D2.2 (A), R10.2
/LED_R: D1.2 (A), R9.2
/QSPI_SCLK: U1.56 (QSPI_SCLK), U3.6 (CLK)
/QSPI_SD0: U1.57 (QSPI_SD0), U3.5 (DI/IO_{0})
/QSPI_SD1: U1.59 (QSPI_SD1), U3.2 (DO/IO_{1})
/QSPI_SD2: U1.58 (QSPI_SD2), U3.3 (~WP/IO_{2})
/QSPI_SD3: U1.55 (QSPI_SD3), U3.7 (~HOLD/~RESET/IO_{3})
/QSPI_SS: R7.1, U1.60 (~QSPI_SS), U3.1 (~CS)
/RUN: J2.37, R8.2, SW5.1, U1.26 (RUN)
/SWCLK: J2.35, U1.24 (SWCLK)
/SWDIO: J2.36, U1.25 (SWDIO)
/USB_CONN_DM: J1.A7 (D-), J1.B7 (D-), R4.1
/USB_CONN_DP: J1.A6 (D+), J1.B6 (D+), R3.1
/USB_DM: R4.2, U1.51 (USB_DM)
/USB_DP: R3.2, U1.52 (USB_DP)
/VREG_AVDD: C14.1, R5.2, U1.46 (VREG_AVDD)
/VREG_LX: L1.1, U1.48 (VREG_LX)
/XIN: C20.1, U1.21 (XIN), Y1.1
/XOUT: R6.1, U1.22 (XOUT)
/XTAL_OUT: C21.1, R6.2, Y1.3
GND: C1.2, C2.2, C3.2, C4.2, C5.2, C6.2, C7.2, C8.2, C9.2, C10.2, C11.2, C12.2, C13.2, C14.2, C15.2, C16.2, C17.2, C18.2, C19.2, C20.2, C21.2, D1.1 (K), D2.1 (K), D3.1 (K), J1.A1 (GND), J1.A12 (GND), J1.B1 (GND), J1.B12 (GND), J1.SH (SHIELD), J2.3, J2.4, J2.38, J2.40, J3.2, R1.2, R2.2, SW1.2, SW2.2, SW3.2, SW4.2, SW5.2, U1.47 (VREG_PGND), U1.61 (GND), U2.2 (GND), U3.4 (GND), Y1.2 (G), Y1.4 (G)
VBUS: C1.1, J1.A4 (VBUS), J1.A9 (VBUS), J1.B4 (VBUS), J1.B9 (VBUS), J2.1, U2.1 (VIN), U2.3 (EN)

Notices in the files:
README.md:
Licence: GPL-3.0-or-later
